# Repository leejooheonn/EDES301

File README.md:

# Hydra-Gotchi | Embedded Smart Scale

**Hydra-Gotchi** is an ARM-based Linux embedded smart scale built on the BeagleBone Black. The system integrates analog force sensing, custom signal calibration software, and interactive user feedback via an I2C OLED display, GPIO digital inputs, and a piezo audio signal.

---

## 📖 Full Build Log & Hardware Schematics

For detailed hardware schematics, wiring diagrams, laser-cut enclosure vectors, and physical build photographs, check out the full project writeup on **Hackster.io**:

👉 **[View the Hydra-Gotchi Project on Hackster.io](https://www.hackster.io/jl587/hydrationhelper-0f8108) 

---

## 🛠️ Hardware & System Architecture

The hardware architecture combines a custom circuit assembly with a laser-cut, stress-tested enclosure designed to standardize physical load distribution across the Force Sensitive Resistor (FSR) to eliminate mechanical measurement noise.

### Hardware Components
* **SBC (Single-Board Computer):** BeagleBone Black (AM335x ARM Cortex-A8)
* **Weight Sensing:** Force Sensitive Resistor (FSR) connected via Analog-to-Digital Converter (ADC)
* **Visual Display:** SSD1306 OLED Display interfaced via **I2C**
* **Inputs & Audio:** Digital push button (**GPIO**) and Piezoelectric Buzzer (**GPIO**)
* **Physical Assembly:** Custom soldered PCB assembly housed in a laser-cut acrylic enclosure

### Block Diagram

```text
  +--------------------------------------------------------------+
  |                      BeagleBone Black                        |
  |                                                              |
  |   +-------------+      +-------------+      +------------+   |
  |   |   ADC Pin   |      |  I2C Bus    |      | GPIO Pins  |   |
  |   +------+------+      +------+------+      +-----+------+   |
  +----------|--------------------|-------------------|----------+
             |                    |                   |
             v                    v                   v
     [ FSR Sensor ]        [ OLED Display ]     [ Push Button / ]
    (Analog Weight)         (128x64 I2C)        [ Piezo Buzzer  ]

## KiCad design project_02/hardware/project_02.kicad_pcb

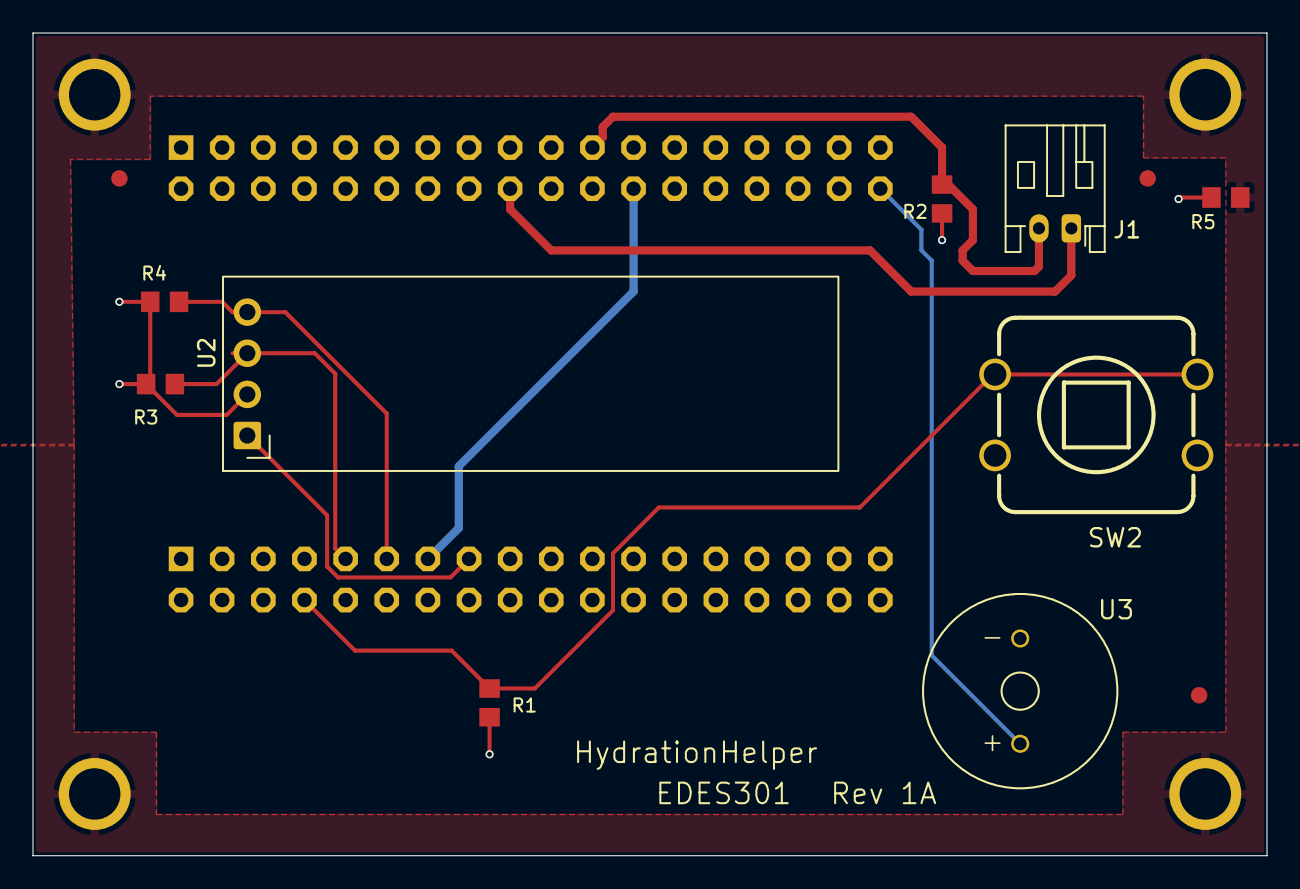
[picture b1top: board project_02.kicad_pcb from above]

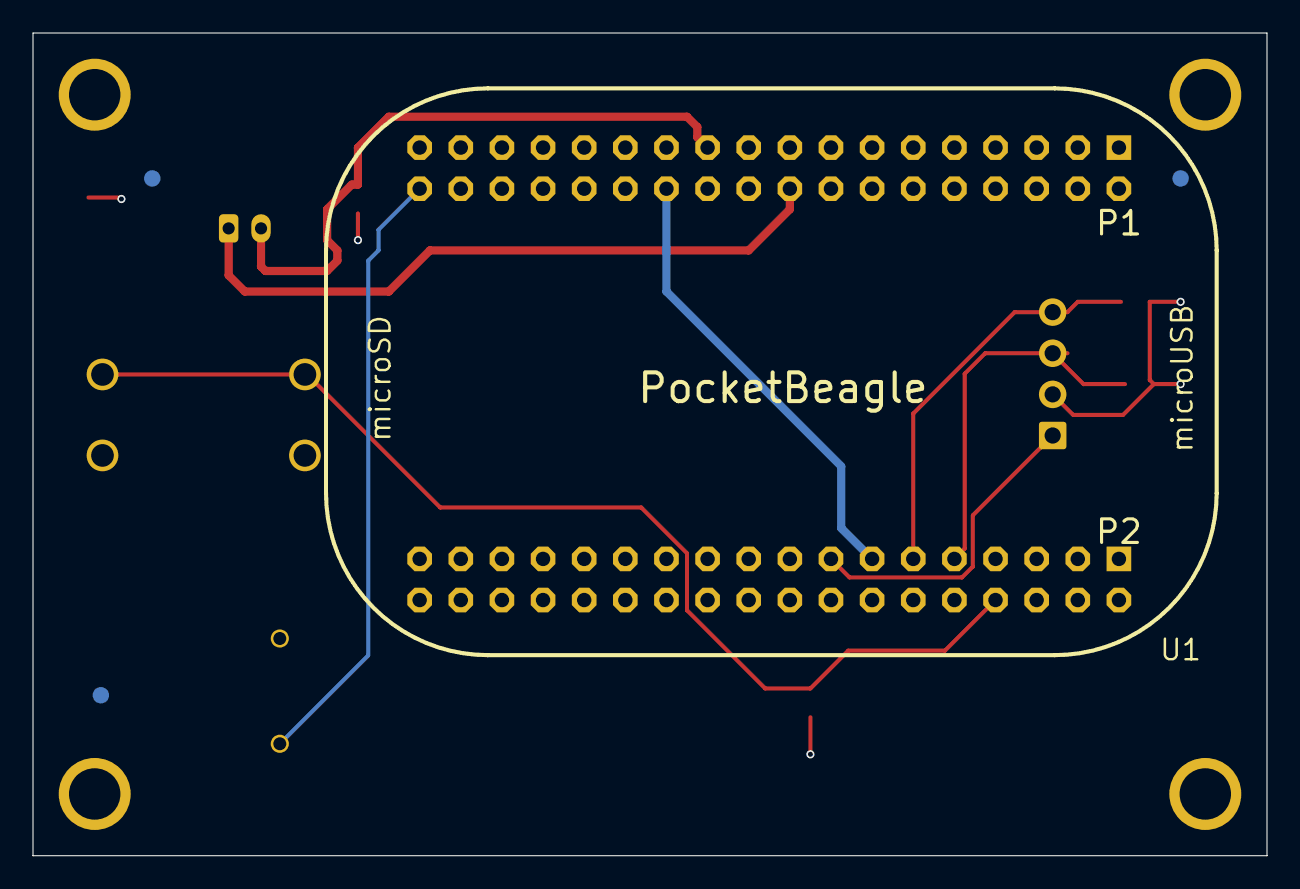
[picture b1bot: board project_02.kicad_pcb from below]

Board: 4 copper layers, 76.2 x 50.8 mm, 20 parts (4 on the bottom side), 10 nets.

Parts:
FUD1, FUD2, FUD3, FUD4, FUD5, FUD6: FIDUCIAL_40MIL
J1: FSR; JST_PH_S2B-PH-K_1x02_P2.00mm_Horizontal
M1, M2, M3, M4: MOUNTING_HOLE
R1: 2.2K; 2.2KR
R2: 30; 30R
R3, R4: DNP; 2.2KR
R5: R0805
SW2: BUTTON_12.5MM
U1: POCKETBEAGLE
U2: SSD1306; ER_OLEDM0.91_1x-I2C
U3: BUZZER_6.5MM

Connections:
+1V8: J1.1, U1.P1_18 (AIN.VREF+)
+3V3: R1.2, R3.1, R4.1, U1.P1_14 (3.3V@1), U1.P2_23 (3.3V@2), U2.2 (VCC)
+5V: U1.P1_24 (VOUT@1), U1.P2_13 (VOUT@2)
/BUTTON: R1.1, SW2.1, SW2.3, U1.P2_08 (GPIO60)
/BUZZER: U1.P1_36 (PWM0A), U3.+
/FSR: J1.2, R2.2, U1.P1_21 (AIN1(1.8V))
/I2C_SCL: R3.2, U1.P2_09 (I2C1.SCL), U2.3 (SCL)
/I2C_SDA: R4.2, U1.P2_11 (I2C1.SDA), U2.4 (SDA)
GND: R2.1, R5.2, SW2.2, SW2.4, U1.P1_15 (GND@1), U1.P1_16 (GND@2), U1.P1_22 (GND@3), U1.P2_15 (GND@4), U1.P2_21 (GND@5), U2.1 (GND), U3.-
GNDPWR: M1.1 (1_1), M2.1 (1_1), M3.1 (1_1), M4.1 (1_1), R5.1

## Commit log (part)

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2026-02-01 Updating README.md
    Added a description for the EDES301 course repository.
2026-02-17 Added simple_calc
2026-02-21 Added more math operators and support for Python 2
2026-02-22 Added blink_led for USR3
2026-02-22 Added licensing and documentation
2026-02-24 Added button functionality for HW 4
2026-04-17 Add button, buzzer, and other project files
2026-04-23 simplified program
2026-04-23 improved ux and overall functionality
2026-05-04 Create project_01
2026-05-04 Create project_01 folder
2026-05-04 Create README.md for project_01
2026-05-04 Create docs
2026-05-04 Create HydrationHelper
2026-05-04 Create README.md for HydrationHelper project
    Added README.md with project details and features.
2026-05-04 Add author section to README.md
2026-05-04 Update README with installation and setup instructions
    Added installation and setup instructions for the project.
2026-05-04 Modify README for running application commands
    Updated instructions to run the application without sudo.
2026-05-04 Rename lee_EDES301_project_01_proposal.key to lee_EDES301_project_01_proposal
2026-05-05 Create EDES301_project_02_mechanical_drawing
2026-05-05 Create mechanical_drawingd
2026-05-06 Add hardware file with initial content
2026-05-06 Create placeholder
2026-05-06 Create hi
